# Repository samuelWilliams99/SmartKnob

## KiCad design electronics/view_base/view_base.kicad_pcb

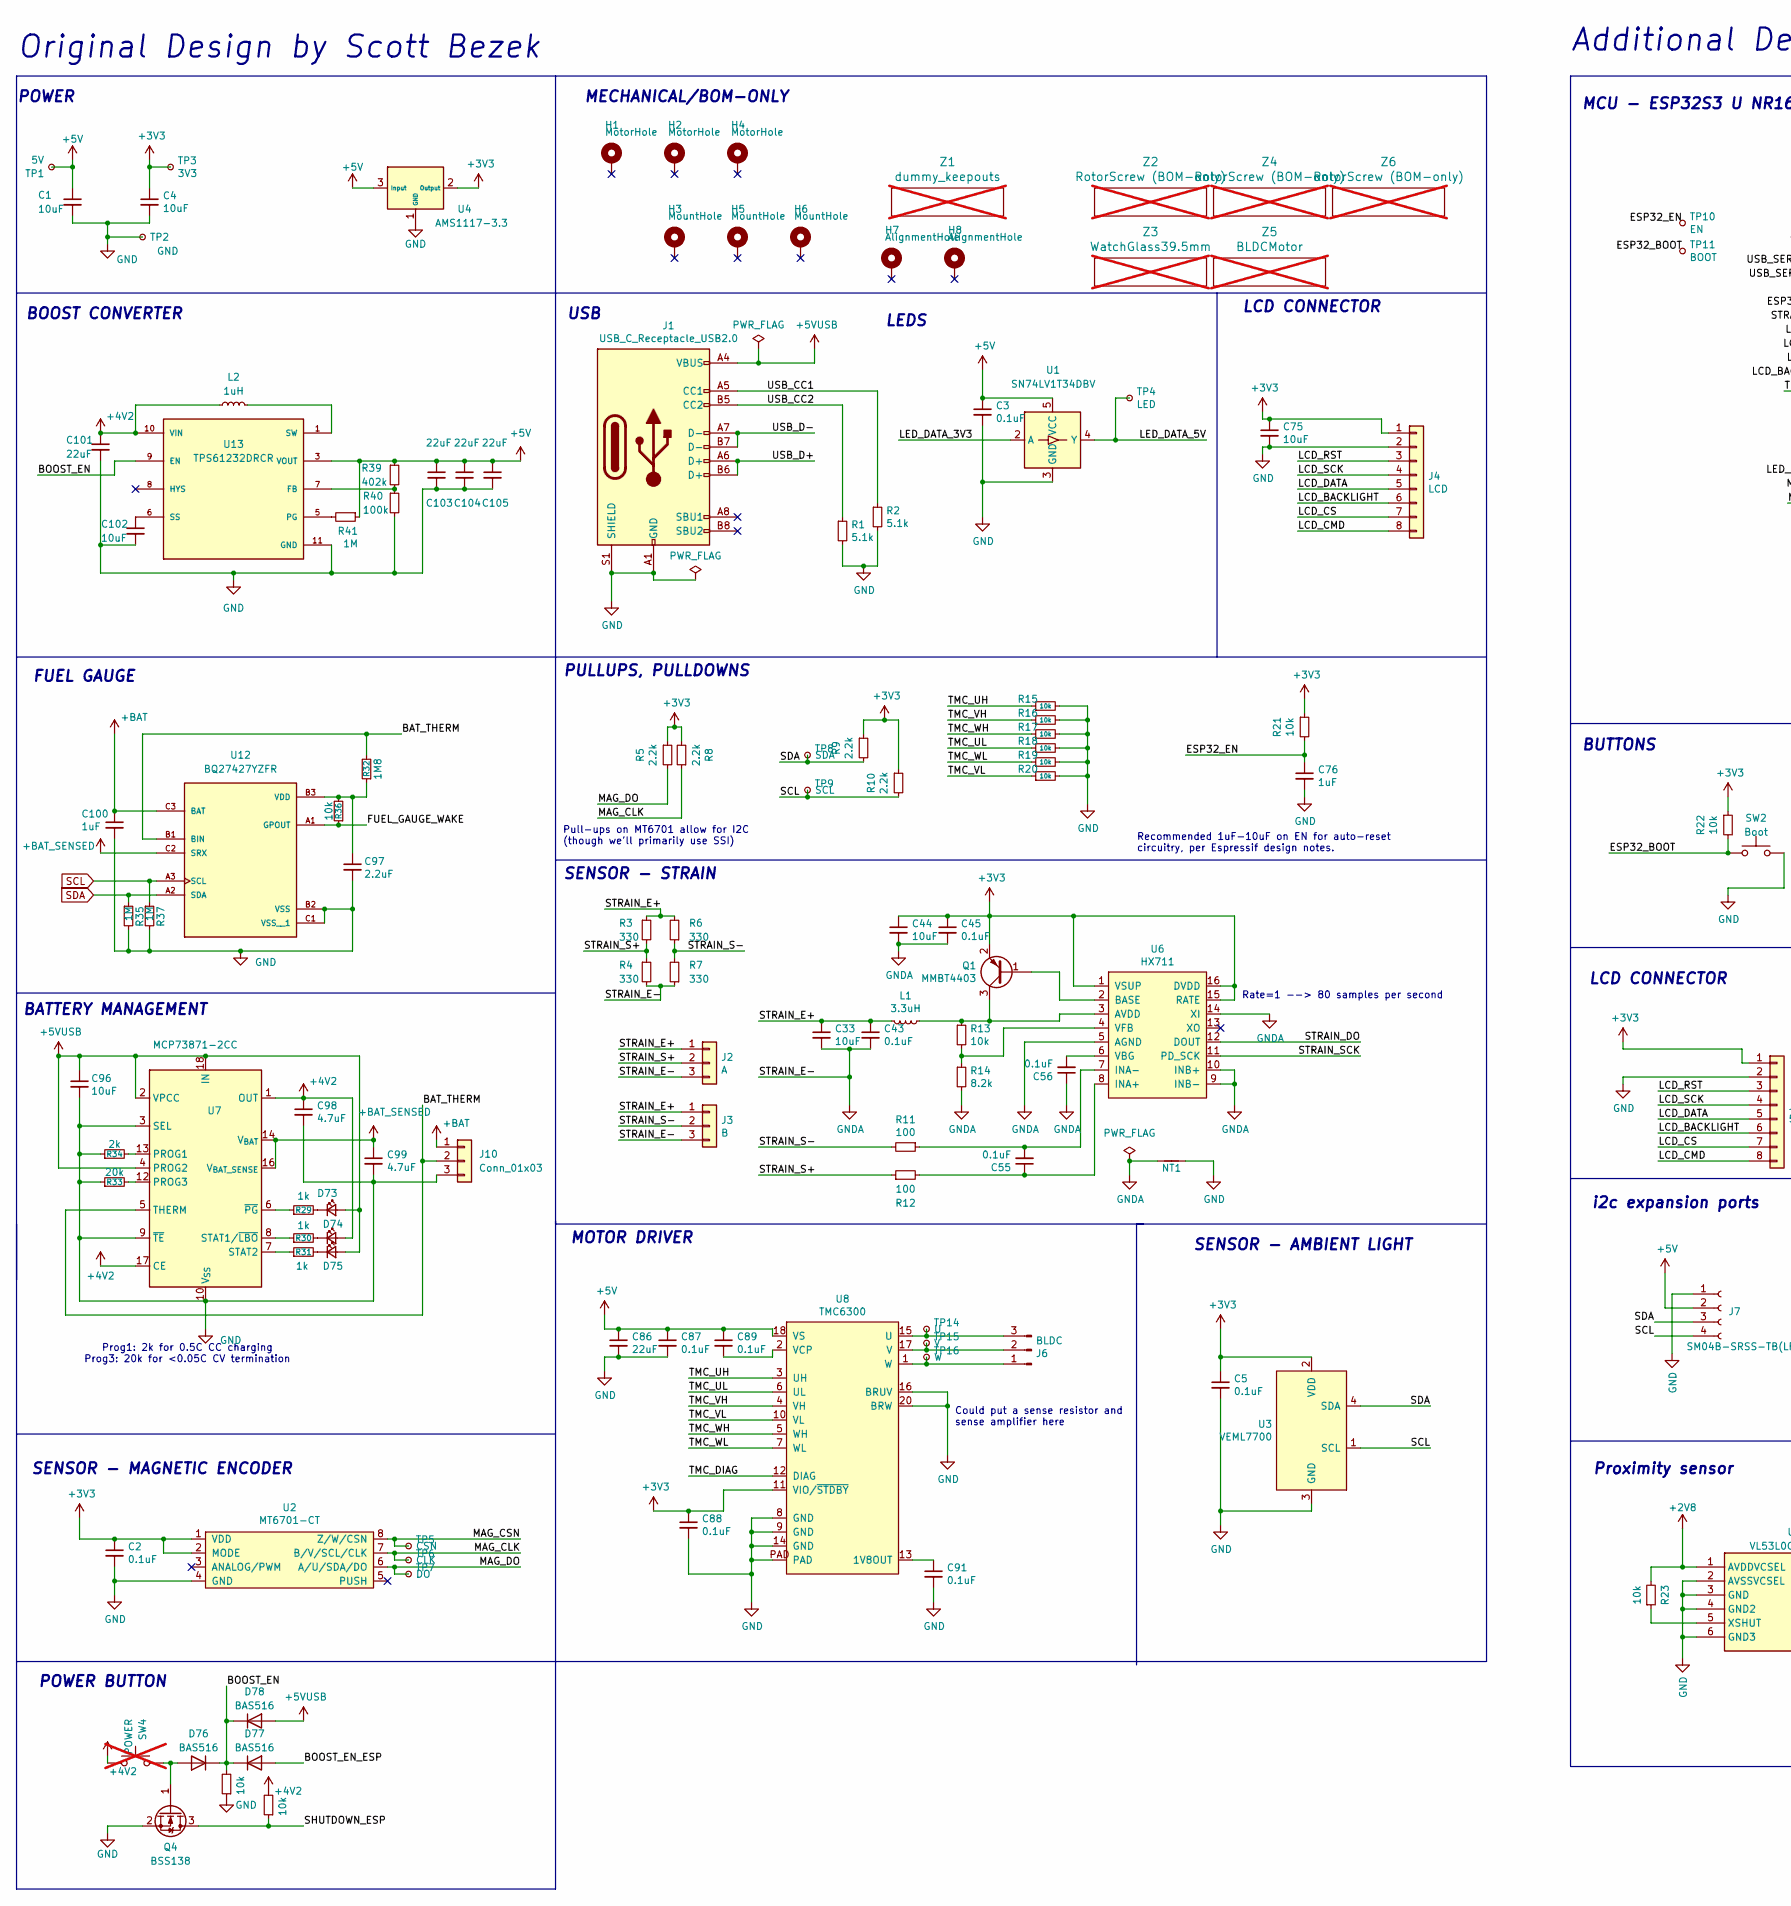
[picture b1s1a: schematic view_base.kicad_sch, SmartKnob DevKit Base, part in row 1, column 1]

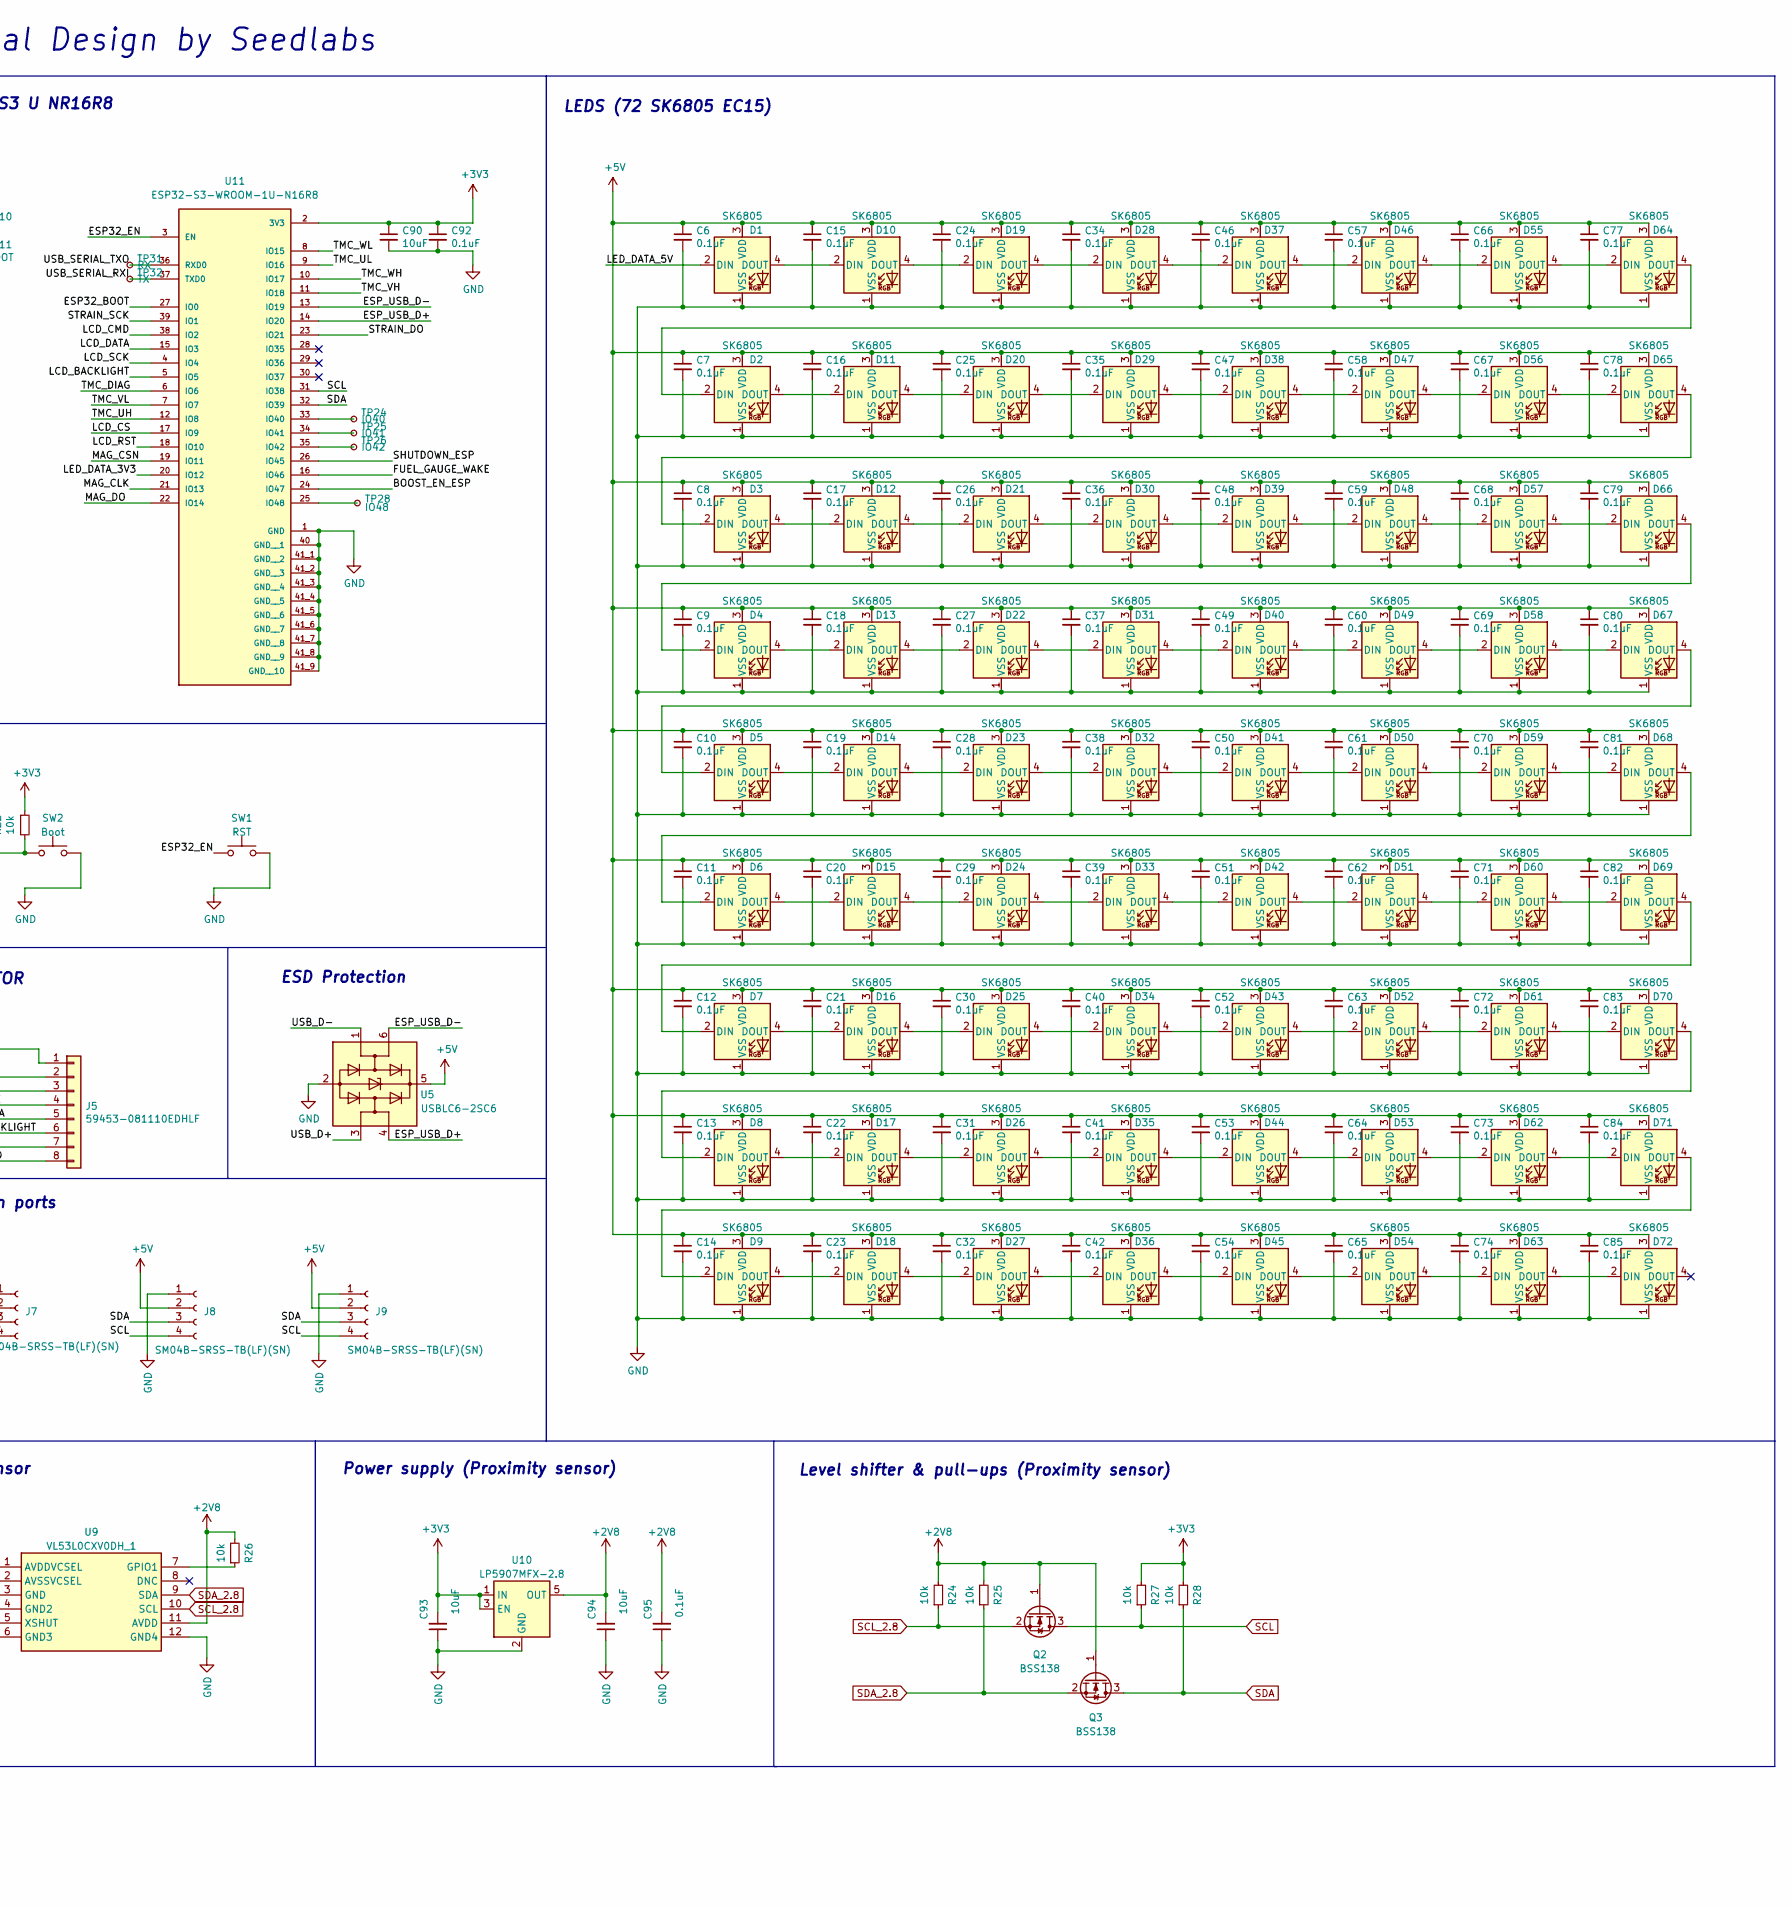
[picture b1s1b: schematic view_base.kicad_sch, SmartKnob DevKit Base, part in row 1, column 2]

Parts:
C1, C4, C33, C44, C75, C90, C96: 10uF; C_0805_2012Metric; LCSC C15850
C2, C3, C5, C43, C45, C55, C56, C87, C88, C89, C91, C92, C95: 0.1uF; C_0603_1608Metric; LCSC C1591
C6, C7, C8, C9, C10, C11, C12, C13, C14, C15, C16, C17, C18, C19, C20, C21, C22, C23, C24, C25, C26, C27, C28, C29, C30, C31, C32, C34, C35, C36, C37, C38, C39, C40, C41, C42, C46, C47, C48, C49, C50, C51, C52, C53, C54, C57, C58, C59, C60, C61, C62, C63, C64, C65, C66, C67, C68, C69, C70, C71, C72, C73, C74, C77, C78, C79, C80, C81, C82, C83, C84, C85: 0.1uF; C_0402_1005Metric; LCSC C83056
C76: 1uF; C_0603_1608Metric; Mouser 187-CL10A105KA8NNNC
C86, C101, C103, C104, C105: 22uF; C_0805_2012Metric; LCSC C98190
C93, C94, C102: 10uF; C_0603_1608Metric; LCSC C38898
C97: 2.2uF; C_0805_2012Metric; LCSC C2228260
C98, C99: 4.7uF; C_0805_2012Metric; LCSC C1779
C100: 1uF; C_0805_2012Metric; LCSC C520051
D1, D2, D3, D4, D5, D6, D7, D8, D9, D10, D11, D12, D13, D14, D15, D16, D17, D18, D19, D20, D21, D22, D23, D24, D25, D26, D27, D28, D29, D30, D31, D32, D33, D34, D35, D36, D37, D38, D39, D40, D41, D42, D43, D44, D45, D46, D47, D48, D49, D50, D51, D52, D53, D54, D55, D56, D57, D58, D59, D60, D61, D62, D63, D64, D65, D66, D67, D68, D69, D70, D71, D72: SK6805; LED_SK6812_EC15_1.5x1.5mm; LCSC C2890035
D73: Blue; LED_0805_2012Metric; LCSC C2293
D74: Green; LED_0805_2012Metric; LCSC C2297
D75: Red; LED_0805_2012Metric; LCSC C2295
D76, D77, D78: BAS516; D_SOD-523; LCSC C10037
H1, H2, H4: MotorHole; MountingHole_M1.6; LCSC C2931389
H3, H5, H6: MountHole; MountingHole_2.2mm_M2_ISO7380_Pad_NonVirtual; LCSC C2911210 or C2911532 (screw), C2961595 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
H7, H8: AlignmentHole; MountingHole_2.2mm_M2_ISO7380_Pad_NonVirtual
J1: USB_C_Receptacle_USB2.0; USB4510_NoPaste; LCSC C428463
J2: A; SolderPads_2mm_3_STRAIN
J3: B; SolderPads_2mm_3_STRAIN
J4: LCD; SolderPads_2mm_8
J5: 59453-081110EDHLF; Amphenol FCI FPC 8 pin 0.5 pitch; Mouser 649-59453081110EDHLF
J6: BLDC; 532610371; LCSC C293630
J7, J8, J9: SM04B-SRSS-TB(LF)(SN); JST_SH_SM04B-SRSS-TB_1x04-1MP_P1.00mm_Horizontal; Mouser 485-4208
J10: Conn_01x03; JST_PH_S3B-PH-K_1x03_P2.00mm_Horizontal; LCSC C545716
L1: 3.3uH; L_0805_2012Metric; LCSC C307744
L2: 1uH; L_0603_1608Metric
NT1: NetTie_2; NetTie-2_SMD_Pad0.5mm
Q1: MMBT4403; SOT-23; LCSC C78864
Q2, Q3, Q4: BSS138; SOT-23; LCSC C2874697
R1, R2: 5.1k; R_0603_1608Metric; LCSC C105580
R3, R4, R6, R7: 330; R_2512_6332Metric; LCSC C19866
R5, R8, R9, R10: 2.2k; R_0603_1608Metric; LCSC C4190
R11, R12: 100; R_0603_1608Metric; LCSC C319953
R13, R15, R16, R17, R18, R19, R20, R21, R22, R23, R24, R25, R26, R27, R28, R36, R42, R43: 10k; R_0603_1608Metric; LCSC C98220
R14: 8.2k; R_0603_1608Metric; LCSC C114637
R29, R30, R31: 1k; R_0603_1608Metric; LCSC C21190
R32: 1M8; R_0603_1608Metric; LCSC C22356606
R33: 20k; R_0805_2012Metric_Pad1.20x1.40mm_HandSolder; LCSC C4328
R34: 2k; R_0805_2012Metric_Pad1.20x1.40mm_HandSolder; LCSC C17604
R35, R37, R41: 1M; R_0603_1608Metric; LCSC C22935
R39: 402k; R_0603_1608Metric; LCSC C23048
R40: 100k; R_0603_1608Metric; LCSC C25803
SW1: RST; SW_SPST_PTS810; LCSC C116501
SW2: Boot; SW_SPST_PTS810; LCSC C116501
SW4: POWER; TestPoint_2Pads_Pitch2.54mm_Drill0.8mm; LCSC C116501; not fitted
TP1: 5V; TestPoint_Pad_D2.0mm
TP2: GND; TestPoint_Pad_D2.0mm
TP3: 3V3; TestPoint_Pad_D2.0mm
TP4: LED; TestPoint_Pad_D2.0mm
TP5: CSN; TestPoint_Pad_D2.0mm
TP6: CLK; TestPoint_Pad_D2.0mm
TP7: DO; TestPoint_Pad_D2.0mm
TP8: SDA; TestPoint_Pad_D2.0mm
TP9: SCL; TestPoint_Pad_D2.0mm
TP10: EN; TestPoint_Pad_D2.0mm
TP11: BOOT; TestPoint_Pad_D2.0mm
TP14: U; TestPoint_Pad_D2.0mm
TP15: V; TestPoint_Pad_D2.0mm
TP16: W; TestPoint_Pad_D2.0mm
TP24: IO40; TestPoint_Pad_D2.0mm
TP25: IO41; TestPoint_Pad_D2.0mm
TP26: IO42; TestPoint_Pad_D2.0mm
TP28: IO48; TestPoint_Pad_D2.0mm
TP31: RX; TestPoint_Pad_D2.0mm
TP32: TX; TestPoint_Pad_D2.0mm
U1: SN74LV1T34DBV; SOT-23-5; LCSC C100024
U2: MT6701-CT; SOIC-8_3.9x4.9mm_P1.27mm; LCSC C2856764
U3: VEML7700; VEML7700-TOP; Digikey VEML7700-TT
U4: AMS1117-3.3; SOT-223-3_TabPin2_GndOutIn; LCSC C6186
U5: USBLC6-2SC6; SOT-23-6; LCSC C7519
U6: HX711; SOIC-16_3.9x9.9mm_P1.27mm; LCSC C43656
U7: MCP73871-2CC; QFN-20-1EP_4x4mm_P0.5mm_EP2.5x2.5mm
U8: TMC6300; QFN-20-1EP_3x3mm_P0.4mm_EP1.65x1.65mm_ThermalVias_LargerVia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; Digikey TMC6300-LA-T
U9: VL53L0CXV0DH_1; LGA12_1; Mouser Part Number 511-VL53L0CXV0DH/1
U10: LP5907MFX-2.8; SOT-23-5; Mouser 595-LP5907MFX-2.8NPB
U11: ESP32-S3-WROOM-1U-N16R8; XCVR_ESP32-S3-WROOM-1U-N16R8; PARTREV v1.1; JLCPCB Position Offset 0,-0.5
U12: BQ27427YZFR; Texas_DSBGA-9_1.62x1.58mm_Layout3x3_P0.5mm; PARTREV December 2022
U13: TPS61232DRCR; VREG_TPS61232DRCR; PARTREV C
Z1: dummy_keepouts; ViewKeepouts3d; not fitted
Z2, Z4, Z6: RotorScrew (BOM-only); bom_only_no_pin; not fitted
Z3: WatchGlass39.5mm; bom_only_no_pin; not fitted
Z5: BLDCMotor; bom_only_no_pin; not fitted

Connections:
+2V8: C94.2, C95.2, Q2.1 (G), Q3.1 (G), R23.2, R24.2, R25.2, R26.2, U9.1 (AVDDVCSEL), U9.11 (AVDD), U10.5 (OUT)
+3V3: C2.1, C4.1, C5.1, C44.1, C45.1, C75.1, C88.1, C90.1, C92.1, C93.2, J4.1, J5.1, Q1.2 (E), R5.1, R8.2, R9.1, R10.1, R21.1, R22.1, R27.2, R28.2, TP3.1, U2.1 (VDD), U2.2 (MODE), U3.2 (VDD), U4.2 (Output), U6.1 (VSUP), U6.15 (RATE), U6.16 (DVDD), U8.11 (VIO/~STDBY), U10.1 (IN), U10.3 (EN), U11.2 (3V3)
+4V2: C98.1, C101.1, D74.2 (A), L2.1, R42.2, SW4.1, U7.1 (OUT), U7.17 (CE), U7.20 (OUT), U13.10 (VIN)
+5V: C1.1, C3.1, C6.1, C7.1, C8.1, C9.1, C10.1, C11.1, C12.1, C13.1, C14.1, C15.1, C16.1, C17.1, C18.1, C19.1, C20.1, C21.1, C22.1, C23.1, C24.1, C25.1, C26.1, C27.1, C28.1, C29.1, C30.1, C31.1, C32.1, C34.1, C35.1, C36.1, C37.1, C38.1, C39.1, C40.1, C41.1, C42.1, C46.1, C47.1, C48.1, C49.1, C50.1, C51.1, C52.1, C53.1, C54.1, C57.1, C58.1, C59.1, C60.1, C61.1, C62.1, C63.1, C64.1, C65.1, C66.1, C67.1, C68.1, C69.1, C70.1, C71.1, C72.1, C73.1, C74.1, C77.1, C78.1, C79.1, C80.1, C81.1, C82.1, C83.1, C84.1, C85.1, C86.1, C87.1, C89.1, C103.1, C104.1, C105.1, D1.3 (VDD), D2.3 (VDD), D3.3 (VDD), D4.3 (VDD), D5.3 (VDD), D6.3 (VDD), D7.3 (VDD), D8.3 (VDD), D9.3 (VDD), D10.3 (VDD), D11.3 (VDD), D12.3 (VDD), D13.3 (VDD), D14.3 (VDD), D15.3 (VDD), D16.3 (VDD), D17.3 (VDD), D18.3 (VDD), D19.3 (VDD), D20.3 (VDD), D21.3 (VDD), D22.3 (VDD), D23.3 (VDD), D24.3 (VDD), D25.3 (VDD), D26.3 (VDD), D27.3 (VDD), D28.3 (VDD), D29.3 (VDD), D30.3 (VDD), D31.3 (VDD), D32.3 (VDD), D33.3 (VDD), D34.3 (VDD), D35.3 (VDD), D36.3 (VDD), D37.3 (VDD), D38.3 (VDD), D39.3 (VDD), D40.3 (VDD), D41.3 (VDD), D42.3 (VDD), D43.3 (VDD), D44.3 (VDD), D45.3 (VDD), D46.3 (VDD), D47.3 (VDD), D48.3 (VDD), D49.3 (VDD), D50.3 (VDD), D51.3 (VDD), D52.3 (VDD), D53.3 (VDD), D54.3 (VDD), D55.3 (VDD), D56.3 (VDD), D57.3 (VDD), D58.3 (VDD), D59.3 (VDD), D60.3 (VDD), D61.3 (VDD), D62.3 (VDD), D63.3 (VDD), D64.3 (VDD), D65.3 (VDD), D66.3 (VDD), D67.3 (VDD), D68.3 (VDD), D69.3 (VDD), D70.3 (VDD), D71.3 (VDD), D72.3 (VDD), J7.2, J8.2, J9.2, R39.1, R41.1, TP1.1, U1.5 (VCC), U4.3 (Input), U5.5 (VBUS), U8.18 (VS), U13.3 (VOUT), U13.4 (VOUT)
+5VUSB: C96.1, D73.2 (A), D75.2 (A), D78.2 (A), J1.A4 (VBUS), J1.A9 (VBUS), J1.B4 (VBUS), J1.B9 (VBUS), U7.2 (VPCC), U7.4 (PROG2), U7.18 (IN), U7.19 (IN)
+BAT: C100.1, J10.1, U12.C3 (BAT)
+BAT_SENSED: C99.1, U7.14 (V_{BAT}), U7.15 (V_{BAT}), U7.16 (V_{BAT_SENSE}), U12.C2 (SRX)
/BAT_THERM: J10.2, R32.2, U7.5 (THERM), U12.B1 (BIN)
/BOOST_EN: D76.1 (K), D77.1 (K), D78.1 (K), R43.2, U13.9 (EN)
/BOOST_EN_ESP: D77.2 (A), U11.24 (IO47)
/ESP32_BOOT: R22.2, SW2.1, TP11.1, U11.27 (IO0)
/ESP32_EN: C76.1, R21.2, SW1.1, TP10.1, U11.3 (EN)
/ESP_USB_D+: U5.4 (I/O2), U11.14 (IO20)
/ESP_USB_D-: U5.6 (I/O1), U11.13 (IO19)
/FUEL_GAUGE_WAKE: R36.1, U11.16 (IO46), U12.A1 (GPOUT)
/LCD_BACKLIGHT: J4.6, J5.6, U11.5 (IO5)
/LCD_CMD: J4.8, J5.8, U11.38 (IO2)
/LCD_CS: J4.7, J5.7, U11.17 (IO9)
/LCD_DATA: J4.5, J5.5, U11.15 (IO3)
/LCD_RST: J4.3, J5.3, U11.18 (IO10)
/LCD_SCK: J4.4, J5.4, U11.4 (IO4)
/LED_DATA_3V3: U1.2 (A), U11.20 (IO12)
/LED_DATA_5V: D1.2 (DIN), TP4.1, U1.4 (Y)
/MAG_CLK: R8.1, TP6.1, U2.7 (B/V/SCL/CLK), U11.21 (IO13)
/MAG_CSN: TP5.1, U2.8 (Z/W/CSN), U11.19 (IO11)
/MAG_DO: R5.2, TP7.1, U2.6 (A/U/SDA/DO), U11.22 (IO14)
/SHUTDOWN_ESP: Q4.3 (D), R42.1, U11.26 (IO45)
/STRAIN_DO: U6.12 (DOUT), U11.23 (IO21)
/STRAIN_E+: C33.1, C43.1, J2.1, J3.1, L1.2, R3.1, R6.2
/STRAIN_S+: J2.2, R3.2, R4.1, R12.1
/STRAIN_S-: J3.2, R6.1, R7.2, R11.2
/STRAIN_SCK: U6.11 (PD_SCK), U11.39 (IO1)
/TMC_DIAG: U8.12 (DIAG), U11.6 (IO6)
/TMC_UH: R15.1, U8.3 (UH), U11.12 (IO8)
/TMC_UL: R18.1, U8.6 (UL), U11.9 (IO16)
/TMC_VH: R16.1, U8.4 (VH), U11.11 (IO18)
/TMC_VL: R20.1, U8.10 (VL), U11.7 (IO7)
/TMC_WH: R17.1, U8.5 (WH), U11.10 (IO17)
/TMC_WL: R19.1, U8.7 (WL), U11.8 (IO15)
/USB_CC1: J1.A5 (CC1), R2.1
/USB_CC2: J1.B5 (CC2), R1.1
/USB_D+: J1.A6 (D+), J1.B6 (D+), U5.3 (I/O2)
/USB_D-: J1.A7 (D-), J1.B7 (D-), U5.1 (I/O1)
/USB_SERIAL_RXI: TP32.1, U11.37 (TXD0)
/USB_SERIAL_TXO: TP31.1, U11.36 (RXD0)
GND: C1.2, C2.2, C3.2, C4.2, C5.2, C6.2, C7.2, C8.2, C9.2, C10.2, C11.2, C12.2, C13.2, C14.2, C15.2, C16.2, C17.2, C18.2, C19.2, C20.2, C21.2, C22.2, C23.2, C24.2, C25.2, C26.2, C27.2, C28.2, C29.2, C30.2, C31.2, C32.2, C34.2, C35.2, C36.2, C37.2, C38.2, C39.2, C40.2, C41.2, C42.2, C46.2, C47.2, C48.2, C49.2, C50.2, C51.2, C52.2, C53.2, C54.2, C57.2, C58.2, C59.2, C60.2, C61.2, C62.2, C63.2, C64.2, C65.2, C66.2, C67.2, C68.2, C69.2, C70.2, C71.2, C72.2, C73.2, C74.2, C75.2, C76.2, C77.2, C78.2, C79.2, C80.2, C81.2, C82.2, C83.2, C84.2, C85.2, C86.2, C87.2, C88.2, C90.2, C91.2, C92.2, C93.1, C94.1, C95.1, C96.2, C97.2, C98.2, C99.2, C100.2, C101.2, C102.2, C103.2, C104.2, C105.2, D1.1 (VSS), D2.1 (VSS), D3.1 (VSS), D4.1 (VSS), D5.1 (VSS), D6.1 (VSS), D7.1 (VSS), D8.1 (VSS), D9.1 (VSS), D10.1 (VSS), D11.1 (VSS), D12.1 (VSS), D13.1 (VSS), D14.1 (VSS), D15.1 (VSS), D16.1 (VSS), D17.1 (VSS), D18.1 (VSS), D19.1 (VSS), D20.1 (VSS), D21.1 (VSS), D22.1 (VSS), D23.1 (VSS), D24.1 (VSS), D25.1 (VSS), D26.1 (VSS), D27.1 (VSS), D28.1 (VSS), D29.1 (VSS), D30.1 (VSS), D31.1 (VSS), D32.1 (VSS), D33.1 (VSS), D34.1 (VSS), D35.1 (VSS), D36.1 (VSS), D37.1 (VSS), D38.1 (VSS), D39.1 (VSS), D40.1 (VSS), D41.1 (VSS), D42.1 (VSS), D43.1 (VSS), D44.1 (VSS), D45.1 (VSS), D46.1 (VSS), D47.1 (VSS), D48.1 (VSS), D49.1 (VSS), D50.1 (VSS), D51.1 (VSS), D52.1 (VSS), D53.1 (VSS), D54.1 (VSS), D55.1 (VSS), D56.1 (VSS), D57.1 (VSS), D58.1 (VSS), D59.1 (VSS), D60.1 (VSS), D61.1 (VSS), D62.1 (VSS), D63.1 (VSS), D64.1 (VSS), D65.1 (VSS), D66.1 (VSS), D67.1 (VSS), D68.1 (VSS), D69.1 (VSS)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
GNDA: C33.2, C43.2, C44.2, C45.2, C56.1, J2.3, J3.3, NT1.1, R4.2, R7.1, R14.2, U6.5 (AGND), U6.9 (INB-), U6.10 (INB+), U6.14 (XI)
unnamed: D1.4 (DOUT), D10.2 (DIN)
unnamed: D2.2 (DIN), D64.4 (DOUT)
unnamed: D3.2 (DIN), D65.4 (DOUT)
unnamed: D4.2 (DIN), D66.4 (DOUT)
unnamed: D5.2 (DIN), D67.4 (DOUT)
unnamed: D6.2 (DIN), D68.4 (DOUT)
unnamed: D10.4 (DOUT), D19.2 (DIN)
unnamed: D2.4 (DOUT), D11.2 (DIN)
unnamed: D11.4 (DOUT), D20.2 (DIN)
unnamed: D3.4 (DOUT), D12.2 (DIN)
unnamed: D12.4 (DOUT), D21.2 (DIN)
unnamed: D4.4 (DOUT), D13.2 (DIN)
unnamed: D13.4 (DOUT), D22.2 (DIN)
unnamed: D5.4 (DOUT), D14.2 (DIN)
unnamed: D14.4 (DOUT), D23.2 (DIN)
unnamed: D6.4 (DOUT), D15.2 (DIN)
unnamed: D15.4 (DOUT), D24.2 (DIN)
unnamed: D7.4 (DOUT), D16.2 (DIN)
unnamed: D16.4 (DOUT), D25.2 (DIN)
unnamed: D8.4 (DOUT), D17.2 (DIN)
unnamed: D17.4 (DOUT), D26.2 (DIN)
unnamed: D9.4 (DOUT), D18.2 (DIN)
unnamed: D18.4 (DOUT), D27.2 (DIN)
unnamed: D19.4 (DOUT), D28.2 (DIN)
unnamed: D20.4 (DOUT), D29.2 (DIN)
unnamed: D21.4 (DOUT), D30.2 (DIN)
unnamed: D22.4 (DOUT), D31.2 (DIN)
unnamed: D23.4 (DOUT), D32.2 (DIN)
unnamed: D24.4 (DOUT), D33.2 (DIN)
unnamed: D25.4 (DOUT), D34.2 (DIN)
unnamed: D26.4 (DOUT), D35.2 (DIN)
unnamed: D27.4 (DOUT), D36.2 (DIN)
unnamed: D28.4 (DOUT), D37.2 (DIN)
unnamed: D29.4 (DOUT), D38.2 (DIN)
unnamed: D30.4 (DOUT), D39.2 (DIN)
unnamed: D31.4 (DOUT), D40.2 (DIN)
unnamed: D32.4 (DOUT), D41.2 (DIN)
unnamed: D33.4 (DOUT), D42.2 (DIN)
unnamed: D34.4 (DOUT), D43.2 (DIN)
unnamed: D35.4 (DOUT), D44.2 (DIN)
unnamed: D36.4 (DOUT), D45.2 (DIN)
unnamed: D37.4 (DOUT), D46.2 (DIN)
unnamed: D38.4 (DOUT), D47.2 (DIN)
unnamed: D39.4 (DOUT), D48.2 (DIN)
unnamed: D40.4 (DOUT), D49.2 (DIN)
unnamed: D41.4 (DOUT), D50.2 (DIN)
unnamed: D42.4 (DOUT), D51.2 (DIN)
unnamed: D43.4 (DOUT), D52.2 (DIN)
unnamed: D44.4 (DOUT), D53.2 (DIN)
unnamed: D45.4 (DOUT), D54.2 (DIN)
unnamed: D46.4 (DOUT), D55.2 (DIN)
unnamed: D47.4 (DOUT), D56.2 (DIN)
unnamed: D48.4 (DOUT), D57.2 (DIN)
unnamed: D49.4 (DOUT), D58.2 (DIN)
unnamed: D50.4 (DOUT), D59.2 (DIN)
unnamed: D51.4 (DOUT), D60.2 (DIN)
unnamed: D52.4 (DOUT), D61.2 (DIN)
unnamed: D53.4 (DOUT), D62.2 (DIN)
unnamed: D54.4 (DOUT), D63.2 (DIN)
unnamed: D55.4 (DOUT), D64.2 (DIN)
unnamed: D56.4 (DOUT), D65.2 (DIN)
unnamed: D57.4 (DOUT), D66.2 (DIN)
unnamed: D58.4 (DOUT), D67.2 (DIN)
unnamed: D59.4 (DOUT), D68.2 (DIN)
unnamed: D60.4 (DOUT), D69.2 (DIN)
unnamed: D61.4 (DOUT), D70.2 (DIN)
unnamed: D62.4 (DOUT), D71.2 (DIN)
unnamed: D63.4 (DOUT), D72.2 (DIN)
unnamed: D7.2 (DIN), D69.4 (DOUT)
unnamed: D8.2 (DIN), D70.4 (DOUT)
unnamed: D9.2 (DIN), D71.4 (DOUT)
unnamed: D73.1 (K), R29.2
unnamed: D74.1 (K), R30.2
unnamed: D75.1 (K), R31.2
unnamed: D76.2 (A), Q4.1 (G), SW4.2
unnamed: J6.1, TP16.1, U8.1 (W)
unnamed: J6.2, TP15.1, U8.17 (V)
unnamed: J6.3, TP14.1, U8.15 (U)
unnamed: Q1.1 (B), U6.2 (BASE)
unnamed: L1.1, Q1.3 (C), R13.1, U6.3 (AVDD)
unnamed: C55.1, R12.2, U6.8 (INA+)
unnamed: C55.2, R11.1, U6.7 (INA-)
unnamed: C56.2, U6.6 (VBG)
unnamed: R13.2, R14.1, U6.4 (VFB)
unnamed: R34.2, U7.13 (PROG1)
unnamed: R33.2, U7.12 (PROG3)
unnamed: R30.1, U7.8 (STAT1/~LBO)
unnamed: R31.1, U7.7 (STAT2)
unnamed: R29.1, U7.6 (~PG)
unnamed: C91.1, U8.13 (1V8OUT)
unnamed: C89.2, U8.2 (VCP)
unnamed: R26.1, U9.7 (GPIO1)
unnamed: R23.1, U9.5 (XSHUT)
unnamed: TP24.1, U11.33 (IO40)
unnamed: TP25.1, U11.34 (IO41)
unnamed: TP26.1, U11.35 (IO42)
unnamed: TP28.1, U11.25 (IO48)
unnamed: C97.1, R32.1, R36.2, U12.B3 (VDD)
unnamed: R39.2, R40.1, U13.7 (FB)
unnamed: R41.2, U13.5 (PG)
unnamed: C102.1, U13.6 (SS)
SCL: J7.4, J8.4, J9.4, Q2.3 (D), R10.2, R27.1, R37.1, TP9.1, U3.1 (SCL), U11.31 (IO38), U12.A3 (SCL)
SCL_2.8: Q2.2 (S), R24.1, U9.10 (SCL)
SDA: J7.3, J8.3, J9.3, Q3.3 (D), R9.2, R28.1, R35.1, TP8.1, U3.4 (SDA), U11.32 (IO39), U12.A2 (SDA)
SDA_2.8: Q3.2 (S), R25.1, U9.9 (SDA)
SW: L2.2, U13.1 (SW), U13.2 (SW)

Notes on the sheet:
POWER
Could put a sense resistor and sense amplifier here
MCU - ESP32S3 U NR16R8
SENSOR - MAGNETIC ENCODER
MOTOR DRIVER
MECHANICAL/BOM-ONLY
Prog1: 2k for 0.5C CC charging Prog3: 20k for <0.05C CV termination
Pull-ups on MT6701 allow for I2C (though we'll primarily use SSI)
Rate=1 --> 80 samples per second
Additional Design by Seedlabs
Proximity sensor
SENSOR - AMBIENT LIGHT
Power supply (Proximity sensor)
BOOST CONVERTER
Original Design by Scott Bezek
Recommended 1uF-10uF on EN for auto-reset circuitry, per Espressif design notes.
BATTERY MANAGEMENT
POWER BUTTON
USB
SENSOR - STRAIN
LEDS
LEDS (72 SK6805 EC15)
BUTTONS
PULLUPS, PULLDOWNS
LCD CONNECTOR
i2c expansion ports
ESD Protection
Level shifter & pull-ups (Proximity sensor)
FUEL GAUGE

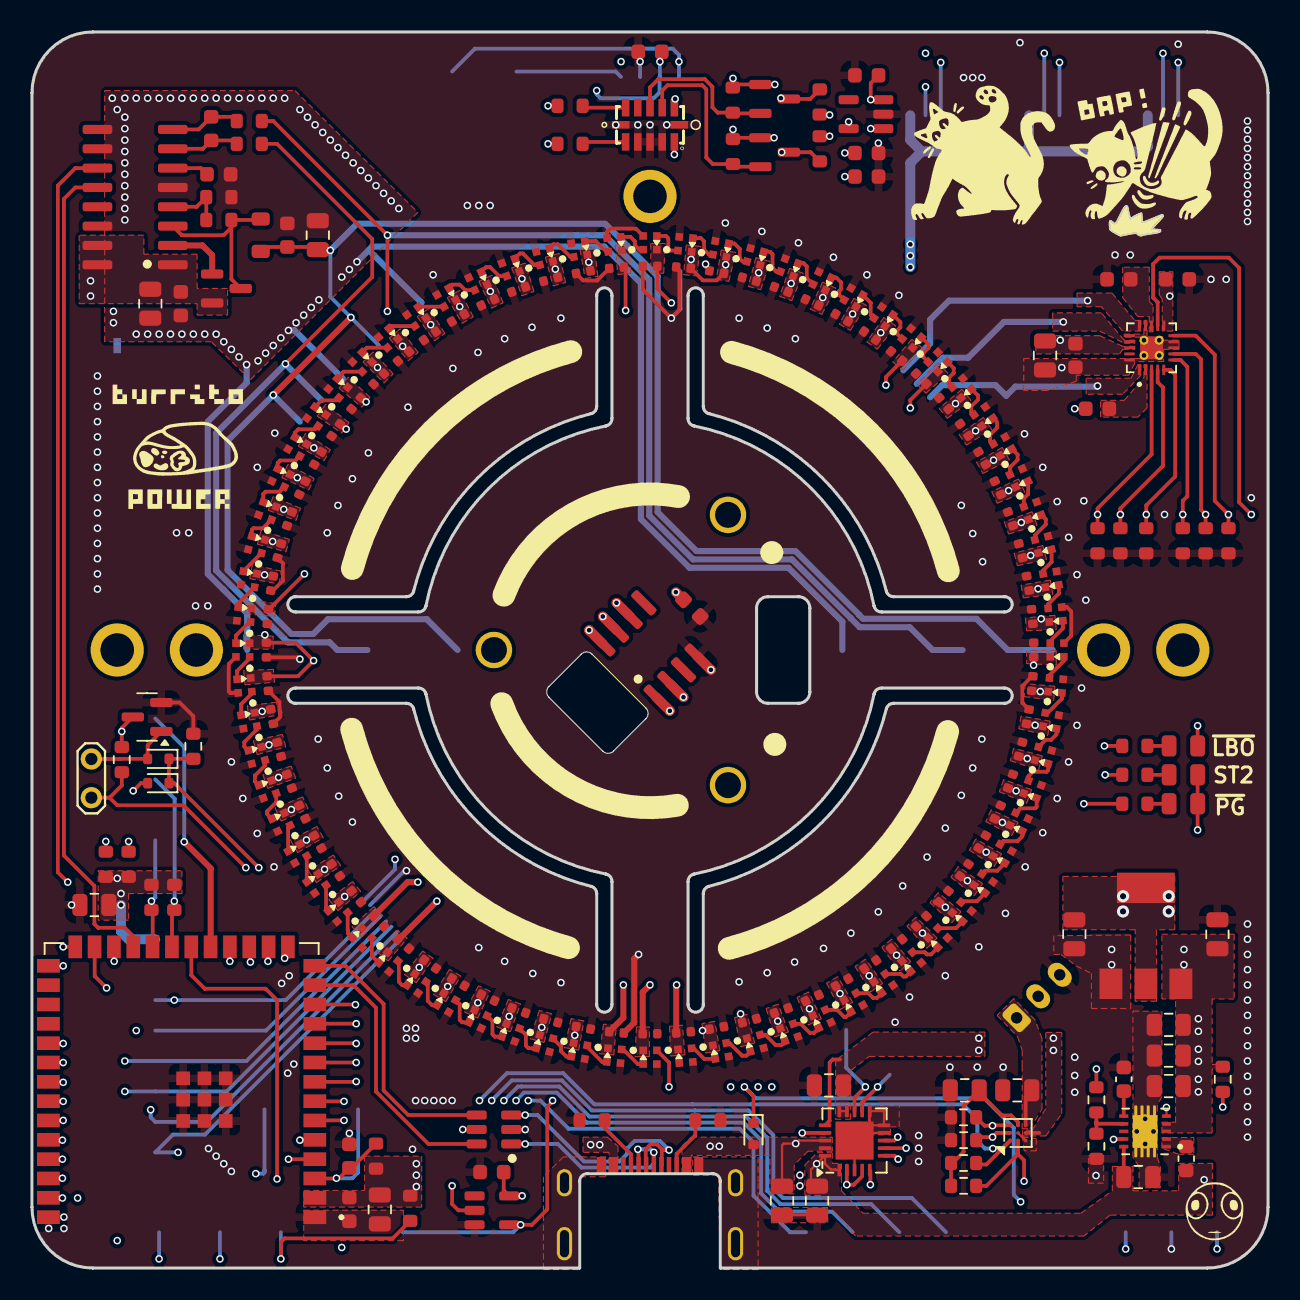
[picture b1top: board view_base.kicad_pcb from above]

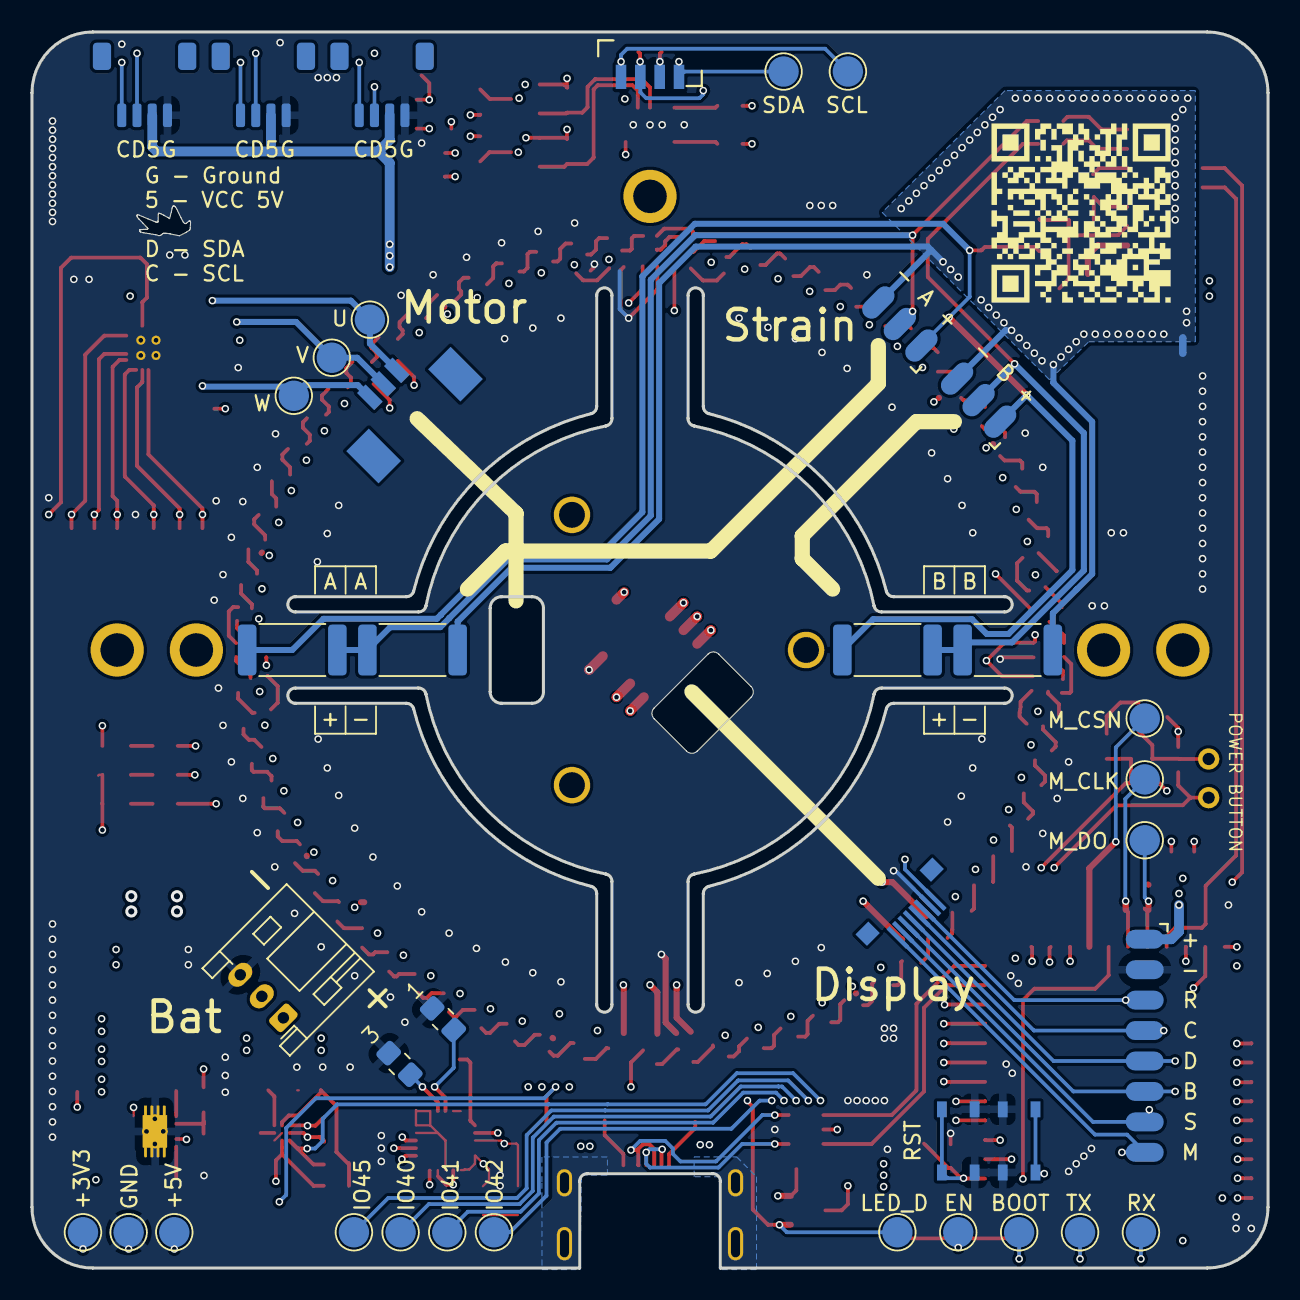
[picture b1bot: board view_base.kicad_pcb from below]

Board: 4 copper layers, 81.2 x 81.2 mm, 291 parts (39 on the bottom side), 153 nets.

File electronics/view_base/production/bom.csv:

Designator,Footprint,Quantity,Value,LCSC Part #
"C1, C33, C4, C44, C75, C90",0805,6,10uF,C15850
"C10, C11, C12, C13, C14, C15, C16, C17, C18, C19, C20, C21, C22, C23, C24, C25, C26, C27, C28, C29, C30, C31, C32, C34, C35, C36, C37, C38, C39, C40, C41, C42, C46, C47, C48, C49, C50, C51, C52, C53, C54, C57, C58, C59, C6, C60, C61, C62, C63, C64, C65, C66, C67, C68, C69, C7, C70, C71, C72, C73, C74, C77, C78, C79, C8, C80, C81, C82, C83, C84, C85, C9",0402,72,0.1uF,C83056
"C2, C3, C43, C45, C5, C55, C56, C87, C88, C89, C91, C92, C95",0603,13,0.1uF,C1591
C76,0603,1,1uF,C5673
C86,0805,1,22uF,C98190
"C93, C94",0603,2,10uF,C38898
"D1, D10, D11, D12, D13, D14, D15, D16, D17, D18, D19, D2, D20, D21, D22, D23, D24, D25, D26, D27, D28, D29, D3, D30, D31, D32, D33, D34, D35, D36, D37, D38, D39, D4, D40, D41, D42, D43, D44, D45, D46, D47, D48, D49, D5, D50, D51, D52, D53, D54, D55, D56, D57, D58, D59, D6, D60, D61, D62, D63, D64, D65, D66, D67, D68, D69, D7, D70, D71, D72, D8, D9",LED_SK6812_EC15_1.5x1.5mm,72,SK6805,C2890035
J1,USB4510_NoPaste,1,USB_C_Receptacle_USB2.0,C428463
J5,Amphenol FCI FPC 8 pin 0.5 pitch,1,59453-081110EDHLF,C5407791
J6,532610371,1,BLDC,C293630
"J7, J8, J9",JST_SH_SM04B-SRSS-TB_1x04-1MP_P1.00mm_Horizontal,3,SM04B-SRSS-TB(LF)(SN),C160404
L1,0805,1,3.3uH,C307744
Q1,SOT-23,1,MMBT4403,C78864
"Q2, Q3",SOT-23,2,BSS138,C2874697
"R1, R2",0603,2,5.1k,C105580
"R10, R5, R8, R9",0603,4,2.2k,C4190
"R11, R12",0603,2,100,C319953
"R13, R15, R16, R17, R18, R19, R20, R21, R22, R23, R24, R25, R26, R27, R28",0603,15,10k,C98220
R14,0603,1,8.2k,C114637
"R3, R4, R6, R7",2512,4,330,C19866
SW1,SW_SPST_PTS810,1,RST,C116501
SW2,SW_SPST_PTS810,1,Boot,C116501
U1,SOT-23-5,1,SN74LV1T34DBV,C100024
U10,SOT-23-5,1,LP5907MFX-2.8,C186700
U11,XCVR_ESP32-S3-WROOM-1U-N16R8,1,ESP32-S3-WROOM-1U-N16R8,C3013946
U2,SOIC-8_3.9x4.9mm_P1.27mm,1,MT6701-CT,C2856764
U3,VEML7700-TOP,1,VEML7700,C1850416
U4,SOT-223-3_TabPin2_GndOutIn,1,AMS1117-3.3,C6186
U5,SOT-23-6,1,USBLC6-2SC6,C7519
U6,SOIC-16_3.9x9.9mm_P1.27mm,1,HX711,C43656
U8,QFN-20-1EP_3x3mm_P0.4mm_EP1.65x1.65mm_ThermalVias_LargerViaHoles,1,TMC6300,505-TMC6300-LA-ND
U9,LGA12_1,1,VL53L0CXV0DH_1,C91199
"Z2, Z4, Z6",bom_only_no_pin,3,RotorScrew (BOM-only),
Z3,bom_only_no_pin,1,WatchGlass39.5mm,
Z5,bom_only_no_pin,1,BLDCMotor,

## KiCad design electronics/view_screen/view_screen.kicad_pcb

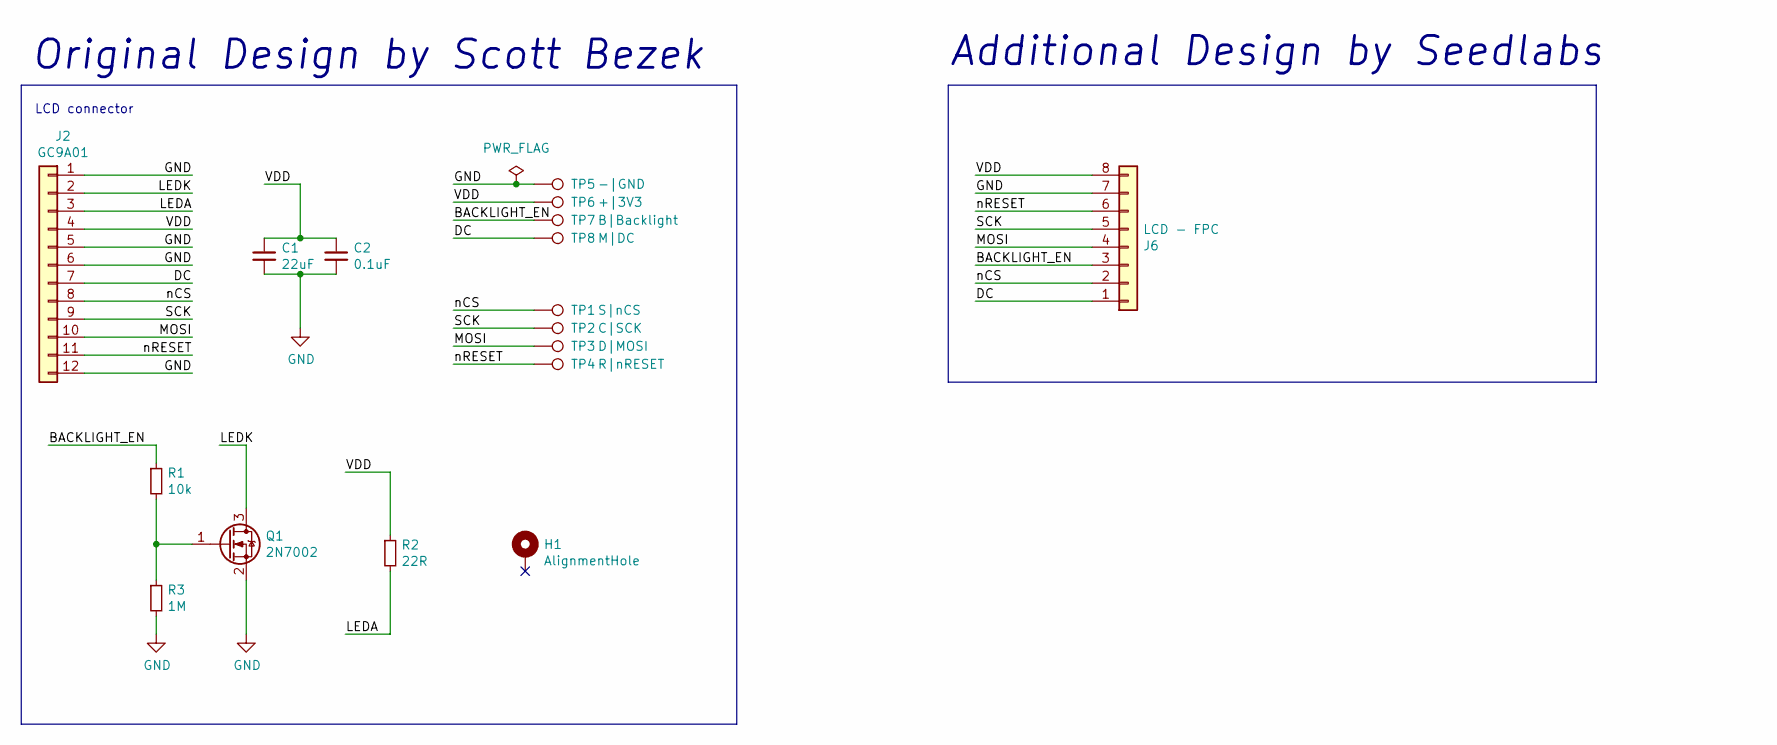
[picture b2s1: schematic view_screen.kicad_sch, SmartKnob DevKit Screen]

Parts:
C1: 22uF; C_0603_1608Metric; Digikey 1276-CL21A226MAYNNNECT-ND
C2: 0.1uF; C_0603_1608Metric; Digikey 1276-1935-1-ND
H1: AlignmentHole; AlignmentHole_1.6
J2: GC9A01; GC9A01Round1.28; Digikey N/A
J6: LCD - FPC; Amphenol FCI FPC 8 pin 0.5 pitch; Mouser 649-59453081110EDHLF
Q1: 2N7002; SOT-23; Digikey 2N7002H6327XTSA2CT-ND
R1: 10k; R_0603_1608Metric; Digikey RMCF0603JT10K0CT-ND
R2: 22R; R_0603_1608Metric; Digikey RMCF0603JT22R0CT-ND
R3: 1M; R_0603_1608Metric; Digikey RMCF0603JT1M00CT-ND
TP1: S|nCS; test_point_connectivity
TP2: C|SCK; test_point_connectivity
TP3: D|MOSI; test_point_connectivity
TP4: R|nRESET; test_point_connectivity
TP5: -|GND; test_point_connectivity
TP6: +|3V3; test_point_connectivity
TP7: B|Backlight; test_point_connectivity
TP8: M|DC; test_point_connectivity

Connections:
/BACKLIGHT_EN: J6.3, R1.1, TP7.1
/DC: J2.7, J6.1, TP8.1
/LEDA: J2.3, R2.2
/LEDK: J2.2, Q1.3 (D)
/MOSI: J2.10, J6.4, TP3.1
/SCK: J2.9, J6.5, TP2.1
/VDD: C1.1, C2.1, J2.4, J6.8, R2.1, TP6.1
/nCS: J2.8, J6.2, TP1.1
/nRESET: J2.11, J6.6, TP4.1
GND: C1.2, C2.2, J2.1, J2.5, J2.6, J2.12, J6.7, Q1.2 (S), R3.2, TP5.1
unnamed: Q1.1 (G), R1.2, R3.1

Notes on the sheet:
Additional Design by Seedlabs
LCD connector
Original Design by Scott Bezek

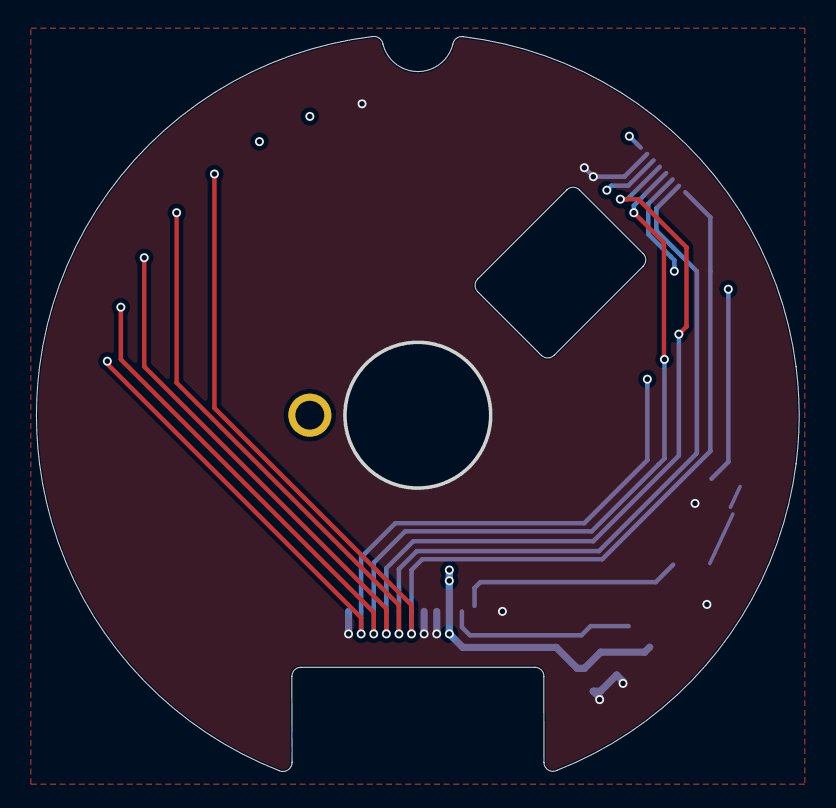
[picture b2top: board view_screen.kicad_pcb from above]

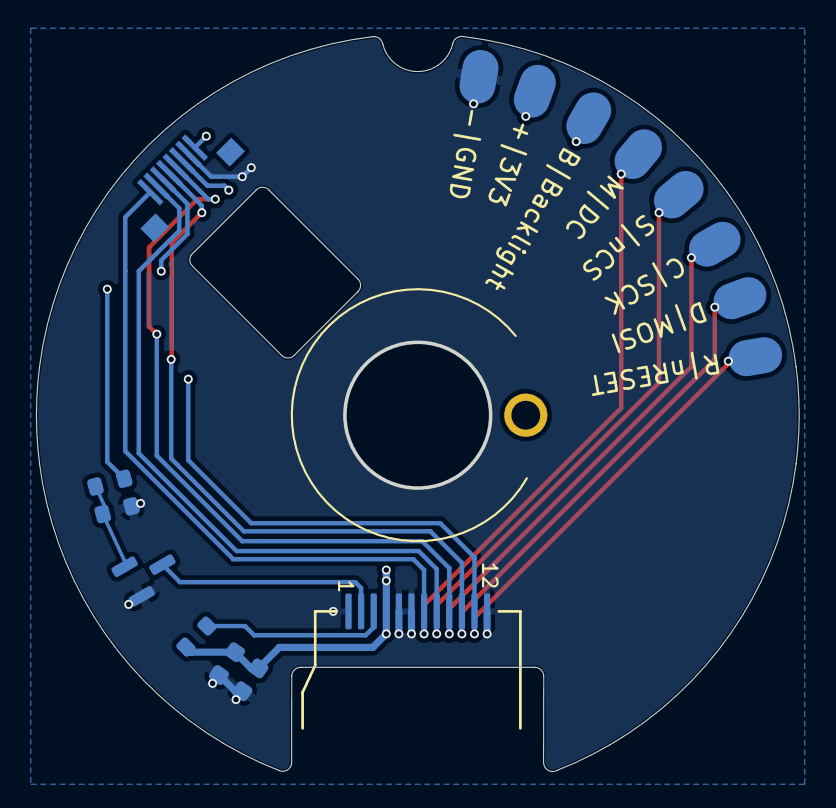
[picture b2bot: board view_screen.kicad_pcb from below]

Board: 4 copper layers, 42.4 x 40.8 mm, 17 parts (16 on the bottom side), 11 nets.

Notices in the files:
parts and their libraries:
Copyright 2021 Accelerated Designs. All rights reserved.
